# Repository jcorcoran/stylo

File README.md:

# stylo

A CR2032 battery operated 555 timer based stylophone modeled after [this](https://www.instructables.com/A-Stylophone/) project.

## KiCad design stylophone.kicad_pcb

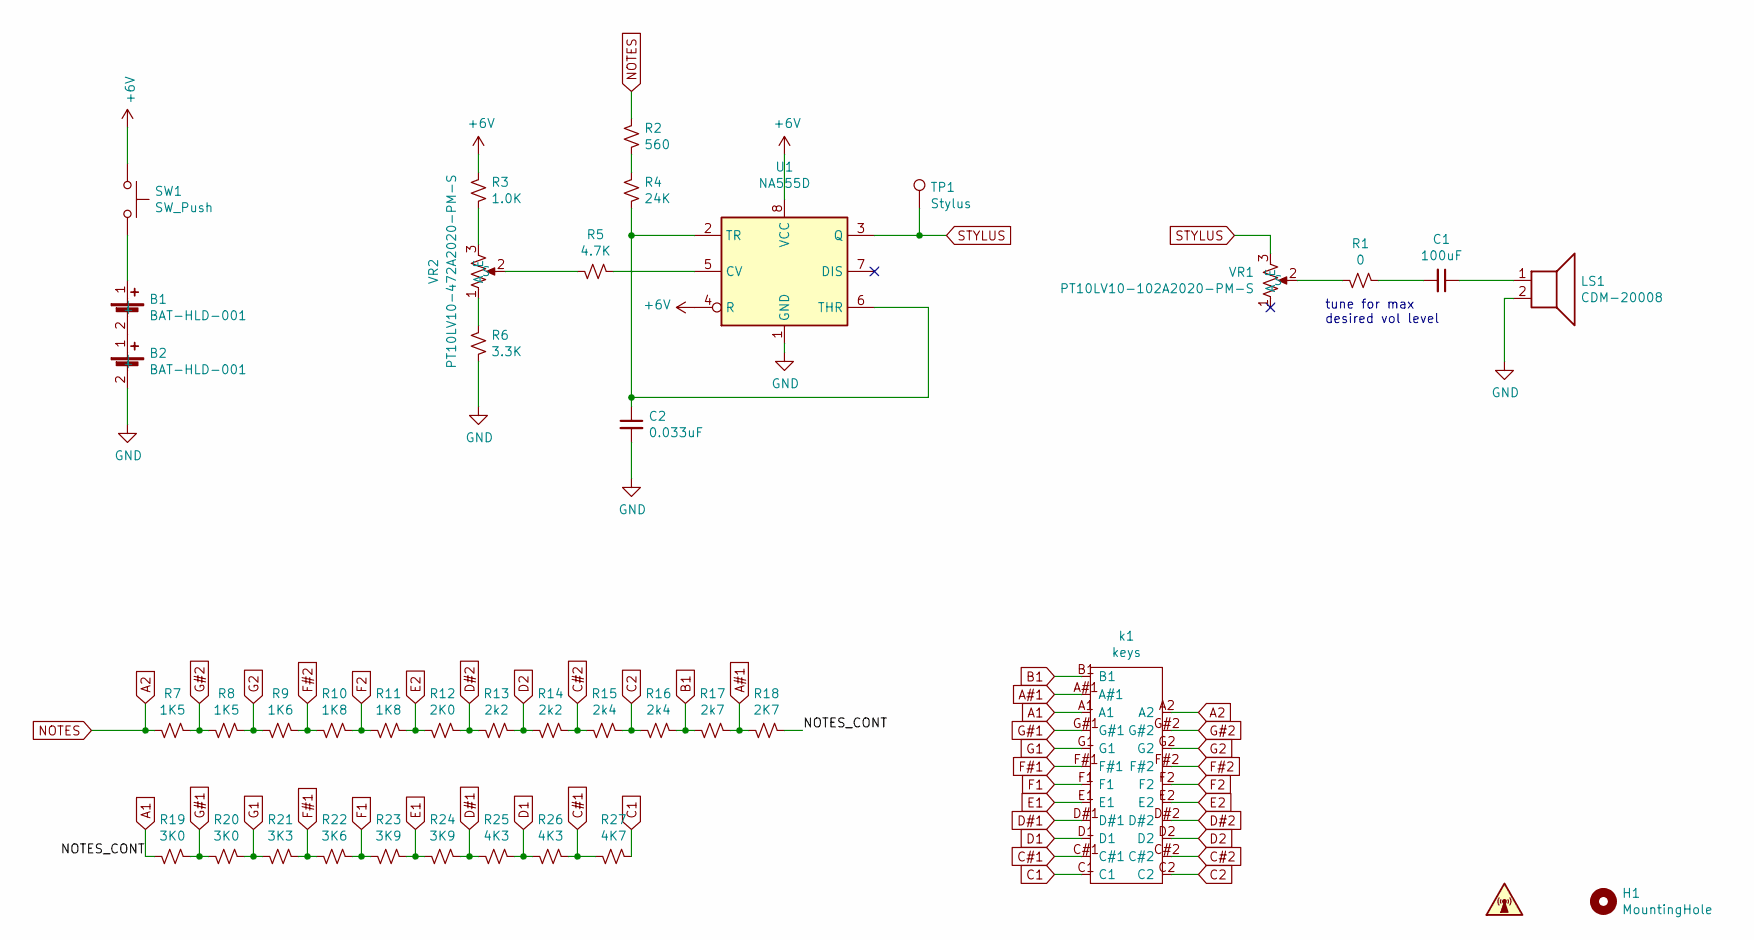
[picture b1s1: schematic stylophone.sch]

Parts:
B1, B2: BAT-HLD-001; BATHLD001; Mouser Part Number 712-BAT-HLD-001
C1: 100uF; C_0805
C2: 0.033uF; C_0805
H1: MountingHole; hole
LOGO1: SYM_Radio_Waves_Small; logo
LS1: CDM-20008; speaker_CDM-20008
R1: 0; R_0805
R2: 560; R_0805
R3: 1.0K; R_0805
R4: 24K; R_0805
R5: 4.7K; R_0805
R6: 3.3K; R_0805
R7, R8: 1K5; R_0805
R9: 1K6; R_0805
R10, R11: 1K8; R_0805
R12: 2K0; R_0805
R13, R14: 2k2; R_0805
R15, R16: 2k4; R_0805
R17: 2k7; R_0805
R18: 2K7; R_0805
R19, R20: 3K0; R_0805
R21: 3K3; R_0805
R22: 3K6; R_0805
R23, R24: 3K9; R_0805
R25, R26: 4K3; R_0805
R27: 4K7; R_0805
SW1: SW_Push; PTS647SM50SMTR2LFS
TP1: Stylus; SolderWire-0.75sqmm_1x01_D1.25mm_OD2.3mm_Relief
U1: NA555D; SOIC-8_3.9x4.9mm_P1.27mm
VR1: PT10LV10-102A2020-PM-S; PT10LV10; Mouser Part Number 531-PT10LV112A22PMS
VR2: PT10LV10-472A2020-PM-S; PT10LV10; Mouser Part Number 531-PT1LV1472A22PMS
k1: keys

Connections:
+6V: R3.1, SW1.1, U1.4 (R), U1.8 (VCC)
A1: R18.1, R19.2, k1.A1
A2: R2.1, R7.2, k1.A2
A#1: R17.1, R18.2, k1.A#1
B1: R16.1, R17.2, k1.B1
C1: R27.1, k1.C1
C2: R15.1, R16.2, k1.C2
C#1: R26.1, R27.2, k1.C#1
C#2: R14.1, R15.2, k1.C#2
D1: R25.1, R26.2, k1.D1
D2: R13.1, R14.2, k1.D2
D#1: R24.1, R25.2, k1.D#1
D#2: R12.1, R13.2, k1.D#2
E1: R23.1, R24.2, k1.E1
E2: R11.1, R12.2, k1.E2
F1: R22.1, R23.2, k1.F1
F2: R10.1, R11.2, k1.F2
F#1: R21.1, R22.2, k1.F#1
F#2: R9.1, R10.2, k1.F#2
G1: R20.1, R21.2, k1.G1
G2: R8.1, R9.2, k1.G2
G#1: R19.1, R20.2, k1.G#1
G#2: R7.1, R8.2, k1.G#2
GND: B2.2 (-), C2.2, LS1.2, R6.2, U1.1 (GND)
unnamed: B1.1 (+), SW1.2
unnamed: B1.2 (-), B2.1 (+)
unnamed: C1.1, LS1.1
unnamed: C1.2, R1.1
unnamed: C2.1, R4.2, U1.2 (TR), U1.6 (THR)
unnamed: R1.2, VR1.2 (S)
unnamed: R2.2, R4.1
unnamed: R3.2, VR2.3 (E)
unnamed: R5.1, U1.5 (CV)
unnamed: R5.2, VR2.2 (S)
unnamed: R6.1, VR2.1 (A)
STYLUS: TP1.1, U1.3 (Q), VR1.3 (E)

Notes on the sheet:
tune for max desired vol level

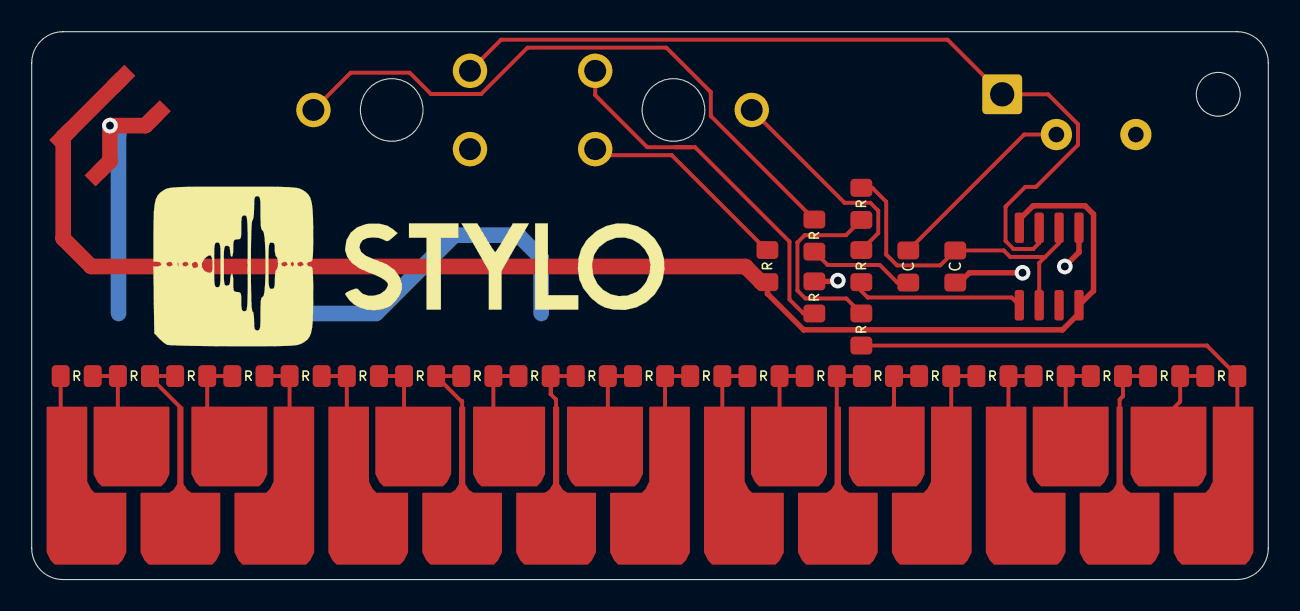
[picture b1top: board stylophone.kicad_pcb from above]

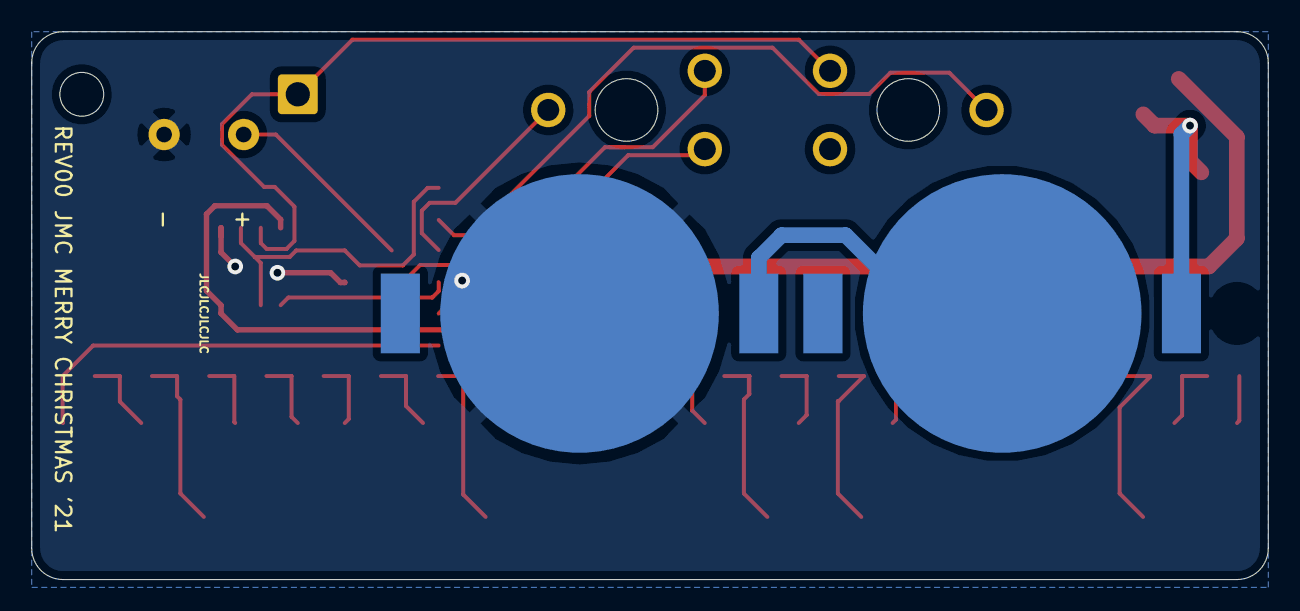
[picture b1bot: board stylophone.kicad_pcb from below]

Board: 2 copper layers, 79.0 x 35.0 mm, 40 parts (3 on the bottom side), 36 nets.
